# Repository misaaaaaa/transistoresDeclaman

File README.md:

# transistoresDeclaman
circuito para instalación sonora basada en compuertas NAND y sistemas imán-bobina caseros

# ruidoRupestre

**Tarjeta de presentación**

Circuito activador de sistema iman-bobina en base a circuito de compuertas NAND y 555 en modo monostable

También utilizada en obra ["Transistores en tránsito"](https://misaa.cc/projects/transistoresentransito.html) (MAC 2025), controlando bobinas suspendidas en la pared

## Revisiones

| Carpeta | Estado |
|---|---|
| [`transistoresDeclaman-rev-a/`](transistoresDeclaman-rev-a/) | Fabricada (JLC Y44-2398046A), THT. Archivos de diseño, esquemático y fotos de esa versión. Solo registro: no editar. |
| [`transistoresDeclaman-rev-b/`](transistoresDeclaman-rev-b/) | En diseño: migración a SMD con ensamblado en JLCPCB (PCBA) y corrección de los issues de rev-a. |

## flujo de trabajo (rev-b)

seguimos el [flujo de partes-jlcpcb](https://github.com/piruetasxyz/partes-jlcpcb/blob/main/flujo.md).

- [x] issues de rev-a corregidos en el esquemático (pin 5 del 555, desacople de U3, Q1)
- [x] esquemático dibujado y ERC sin errores
- [x] partes elegidas en LCSC
- [x] las que faltaban, compradas y en el inventario (ver [partes por comprar](#partes-por-comprar-rev-b-15-placas))
- [x] campo `LCSC` lleno en cada símbolo que se ensambla; `bom.csv` actualizado
- [x] biblioteca local generada con `generar_biblioteca.py` y huellas asignadas
- [x] placa diseñada, zonas rellenas
- [x] DRC sin errores, con paridad entre esquemático y placa
- [x] archivos generados con `generar_fabricacion.py` y commiteados
- [ ] vista previa de JLCPCB revisada pieza por pieza

## partes por comprar (rev-b, 15 placas)

partes que no están en el [inventario de JLCPCB](https://github.com/misaaaaaa/partes-jlcpcb-fork/blob/main/partes_updated.csv). se sacan de acá a medida que se confirma la compra. los mínimos son por placa × 15, sin repuesto: conviene sumar ~10 % y revisar el mínimo de compra de JLCPCB.

### SMD, ensambladas por JLCPCB

todas compradas y en el inventario (2026-11-27): C17673, C8678, C8512, C6986, C99124 y C2128.

### THT, soldadas a mano

| Parte | Referencias | Por placa | Mínimo (15) |
|---|---|---|---|
| CD4093BE (DIP-14), con zócalo | U1, U2 | 2 | 30 |
| LED amarillo 3 mm | D1–D7, D9, D11 | 9 | 135 |
| Trimpot 100k vertical (tipo Runtron RM-065) | RV1–RV4 | 4 | 60 |
| Jack DC horizontal | J2, J3 | 2 | 30 |
| Header 2×3, 2,54 mm | J1 | 1 | 15 |
| Header 1×2, 2,54 mm | J4 | 1 | 15 |
| Jumper 2,54 mm | J1, J4 | 2 | 30 |

## Esquemático rev-a

- Control de frecuencia de 3 osciladores por medio de trimpots

- Visualización de estados por medio de LEDS

- Poesía basada en Jussi Parikka

### Issues rev-a (JLC Y44-2398046A) 

- Pin 5 de 555 NO debe ir a tierra directamente

- Q1 tiene comportamiento extraño. No ubicar y puentear pines 2 y 3

- D13 es demasiado brillante, se recomienda no instalar. Se podría instalar una resistencia más grande en R14

- Las bobinas deben ser de alrededor de 8 a 12 ohm

## BOM rev-a

| Reference                                     | Value       | Footprint                 | Qty |
|------------------------------------------     |-------------|---------------------------|-----|
| R1,R2,R3,R5,R6,R7,R8,R10,R12,R13,~R14~,R16    | 1k          | Resistencia SMD 0805      |  12 |
| U4                                            | L7805       | Regulador TO-252          |   1 |
| U3                                       | Socket      | DIP-8                     |   1 |
| U1,U2                                    | Socket      | DIP-14                    |   2 |
| R11,R15                                  | 100k        | Resistencia THT           |   2 |
| R4,~R9~,R17                                | 10k         | Resistencia THT           |   3 |
| D4,D5,D6                                 | 1N4148      | Diodo                     |   3 |
| D11,D14                                  | 1N4007      | Diodo                     |   2 |
| Q1*,Q3                                    | 2n2222      | Transistor to-92          |   2 |
| C6,C8,C9,C11                             | 100n        | Condensador               |   4 |
| C1,C2,C3,C10                             | 100uF       | Condensador Electrolítico |   4 |
| C4,C5,C7,C12                             | 10uF        | Condensador Electrolítico |   4 |
| D1,D2,D3,D7,D8,D9,D10,D12,~D13~          | LED         | Led 3mm                   |   9 |
| J3,J5                                    | JUMPER      | Pin header 2              |   2 |
| RV1,RV2,RV3                              | 100k        | Trim RM-065               |   3 |
| Q2                                       | IRFZ44n     | Transistor to-220         |   1 |
| J1,J2                                    | Barrel_Jack | Jack DC 2.1mm             |   2 |
| J3,~J5~                                    | JUMPER      | Jumper 2p                 |   2 |
| U3                                       | NE555P      | DIP-8                     |   1 |
| U1,U2                                    | CD4093      | DIP-14                    |   2 |

\* Reemplazar por puente entre pines 2 y 3

## Expo MAC

Foto: Clo Rojo

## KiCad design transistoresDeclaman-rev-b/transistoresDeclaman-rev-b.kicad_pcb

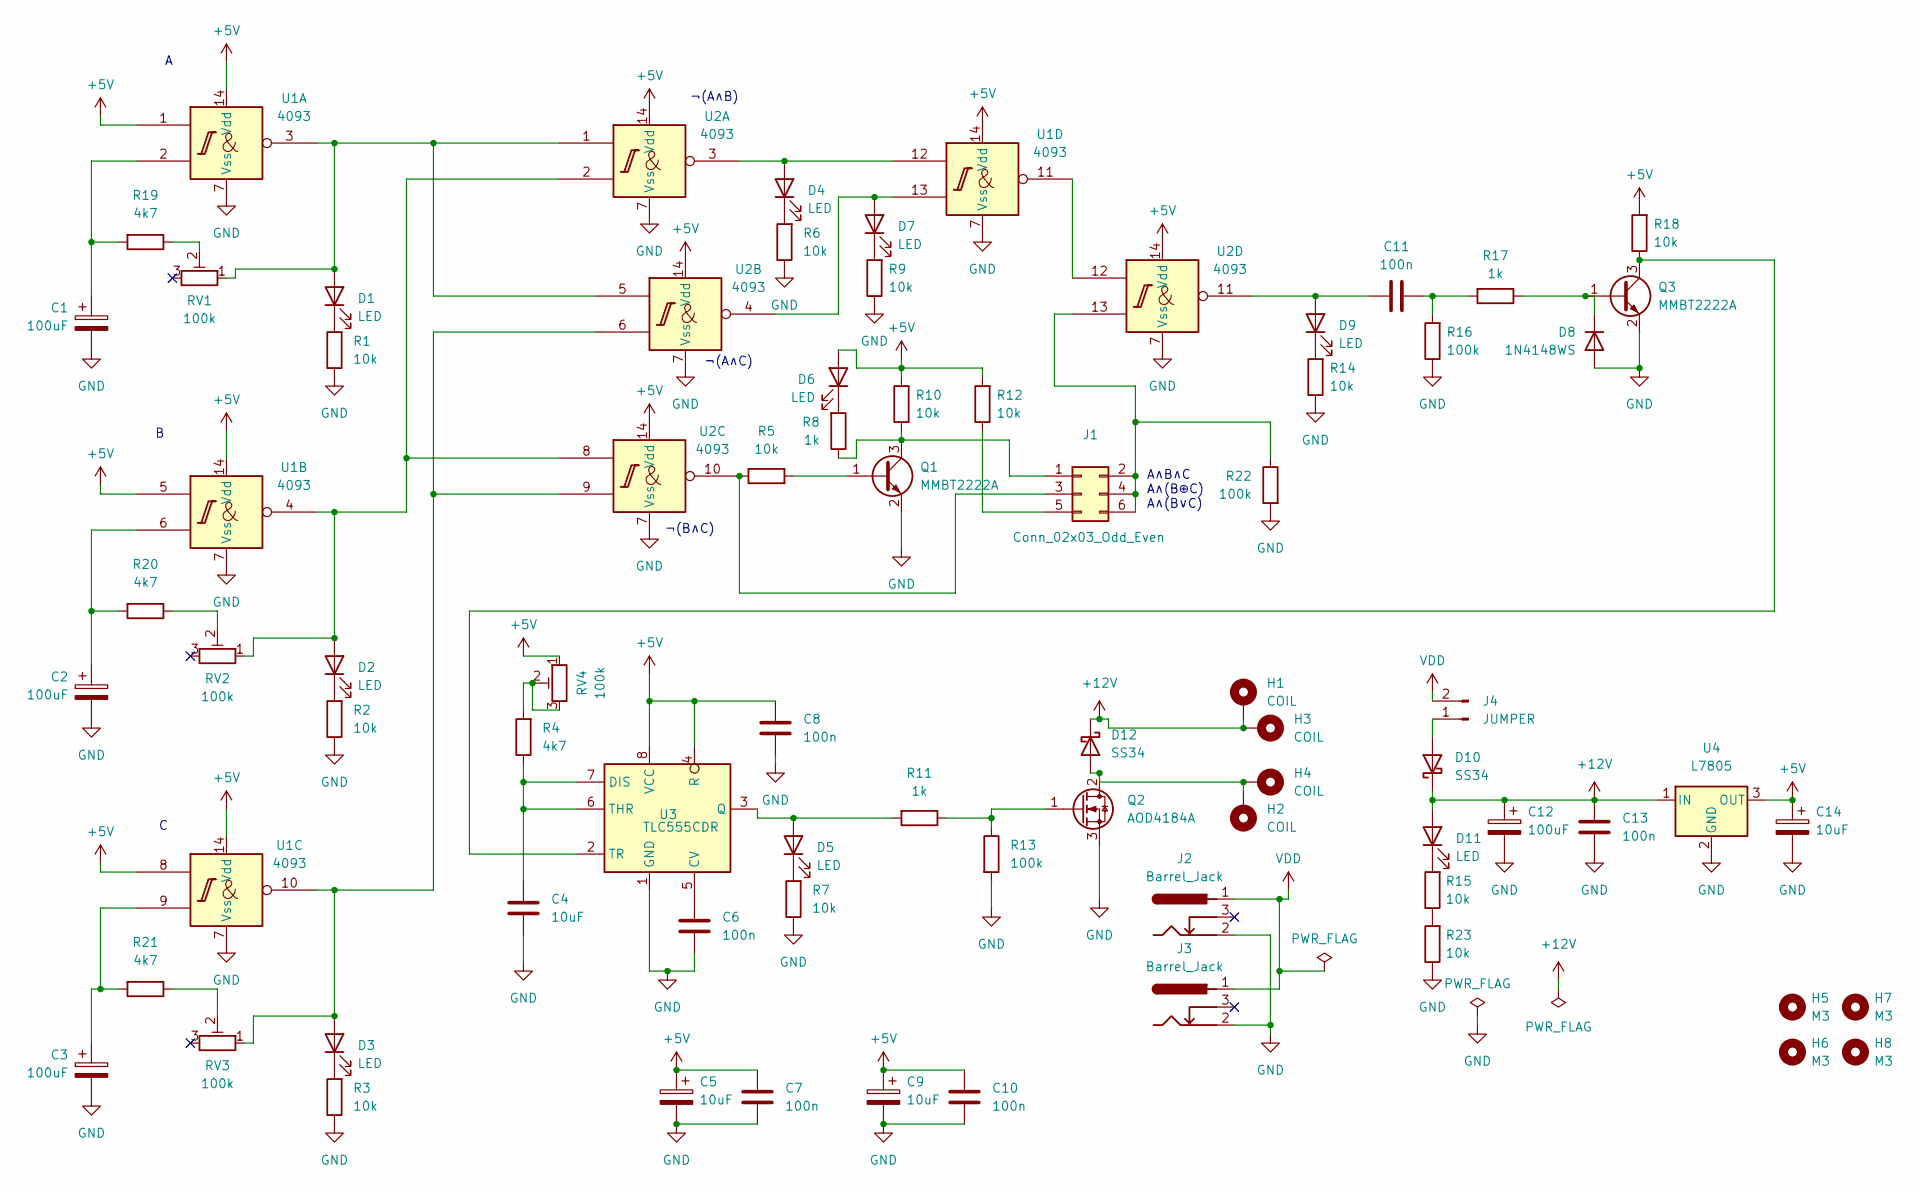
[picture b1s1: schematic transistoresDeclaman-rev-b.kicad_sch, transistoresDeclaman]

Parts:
C1, C2, C3, C12: 100uF; CAP-SMD_BD6.3-L6.6-W6.6-LS7.6-FD; LCSC C72478
C4, C5, C9, C14: 10uF; C1206; LCSC C13585
C6, C7, C8, C10, C11, C13: 100n; C0805; LCSC C49678
D1, D2, D3, D4, D5, D6, D7, D9, D11: LED; LED_PCBasDiffuser
D8: 1N4148WS; SOD-323_L1.8-W1.3-LS2.5-RD; LCSC C2128
D10, D12: SS34; SMA_L4.3-W2.6-LS5.2-RD; LCSC C8678
H1, H2: COIL; TestPoint_Pad_4.0x4.0mm
H3, H4: COIL; TestPoint_THTPad_D4.0mm_Drill2.0mm
H5, H6, H7, H8: M3; MountingHole_3.2mm_M3
J1: Conn_02x03_Odd_Even; PinHeader_2x03_P2.54mm_Vertical
J2, J3: Barrel_Jack; BarrelJack_Horizontal
J4: JUMPER; PinHeader_1x02_P2.54mm_Vertical
Q1, Q3: MMBT2222A; SOT-23-3_L2.9-W1.3-P1.90-LS2.4-BR; LCSC C8512
Q2: AOD4184A; TO-252-2_L6.6-W6.1-P4.57-LS9.9-TL-CW; LCSC C99124
R1, R2, R3, R5, R6, R7, R9, R10, R12, R14, R15, R18, R23: 10k; R0805; LCSC C17414
R4, R19, R20, R21: 4k7; R0805; LCSC C17673
R8, R11, R17: 1k; R0805; LCSC C2907232
R13, R16, R22: 100k; R0805; LCSC C25611
RV1, RV2, RV3, RV4: 100k; Potentiometer_Runtron_RM-065_Vertical
U1, U2: 4093; DIP-14_W7.62mm_LongPads
U3: TLC555CDR; SOIC-8_L5.0-W4.0-P1.27-LS6.0-BL; LCSC C6986
U4: L7805; TO-252-2_L6.6-W6.1-P4.57-LS9.9-BR-CW; LCSC C19626525

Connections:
+5V: C5.1, C7.1, C8.1, C9.1, C10.1, C14.1, D6.2 (A), R10.2, R12.2, R18.2, RV4.1, U1.1, U1.5, U1.8, U1.14 (Vdd), U2.14 (Vdd), U3.4 (R), U3.8 (VCC), U4.3 (OUT)
+12V: C12.1, C13.1, D10.1 (K), D11.2 (A), D12.1 (K), H1.1 (1_1), H3.1 (1_1), U4.1 (IN)
GND: C1.2, C2.2, C3.2, C4.2, C5.2, C6.2, C7.2, C8.2, C9.2, C10.2, C12.2, C13.2, C14.2, D8.2 (A), J2.2, J3.2, Q1.2 (E), Q2.3 (S), Q3.2 (E), R1.1, R2.1, R3.1, R6.1, R7.1, R9.1, R13.2, R14.1, R16.1, R22.2, R23.1, U1.7 (Vss), U2.7 (Vss), U3.1 (GND), U4.2 (GND)
unnamed: C1.1, R19.2, U1.2
unnamed: C2.1, R20.2, U1.6
unnamed: C3.1, R21.2, U1.9
unnamed: C11.2, R16.2, R17.2
unnamed: D1.2 (A), RV1.1, U1.3, U2.1, U2.5
unnamed: D1.1 (K), R1.2
unnamed: D2.2 (A), RV2.1, U1.4, U2.2, U2.8
unnamed: D2.1 (K), R2.2
unnamed: D3.2 (A), RV3.1, U1.10, U2.6, U2.9
unnamed: D3.1 (K), R3.2
unnamed: D4.2 (A), U1.12, U2.3
unnamed: D4.1 (K), R6.2
unnamed: D5.2 (A), R11.2, U3.3 (Q)
unnamed: D5.1 (K), R7.2
unnamed: D6.1 (K), R8.2
unnamed: D7.2 (A), U1.13, U2.4
unnamed: D7.1 (K), R9.2
unnamed: D8.1 (K), Q3.1 (B), R17.1
unnamed: C11.1, D9.2 (A), U2.11
unnamed: D9.1 (K), R14.2
unnamed: D10.2 (A), J4.1
unnamed: D11.1 (K), R15.2
unnamed: D12.2 (A), H2.1 (1_1), H4.1 (1_1), Q2.2 (D)
unnamed: J1.1, Q1.3 (C), R8.1, R10.1
unnamed: J1.2, J1.4, J1.6, R22.1, U2.13
unnamed: J1.3, R5.1, U2.10
unnamed: J1.5, R12.1
unnamed: Q1.1 (B), R5.2
unnamed: Q2.1 (G), R11.1, R13.1
unnamed: Q3.3 (C), R18.1, U3.2 (TR)
unnamed: R4.2, RV4.2, RV4.3
unnamed: R15.1, R23.2
unnamed: R19.1, RV1.2
unnamed: R20.1, RV2.2
unnamed: R21.1, RV3.2
unnamed: U1.11, U2.12
unnamed: C6.1, U3.5 (CV)
unnamed: C4.1, R4.1, U3.6 (THR), U3.7 (DIS)
VDD: J2.1, J3.1, J4.2

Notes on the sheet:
¬(A∧B)
¬(A∧C)
¬(B∧C)
A∧B∧C A∧(B⊕C) A∧(B∨C)

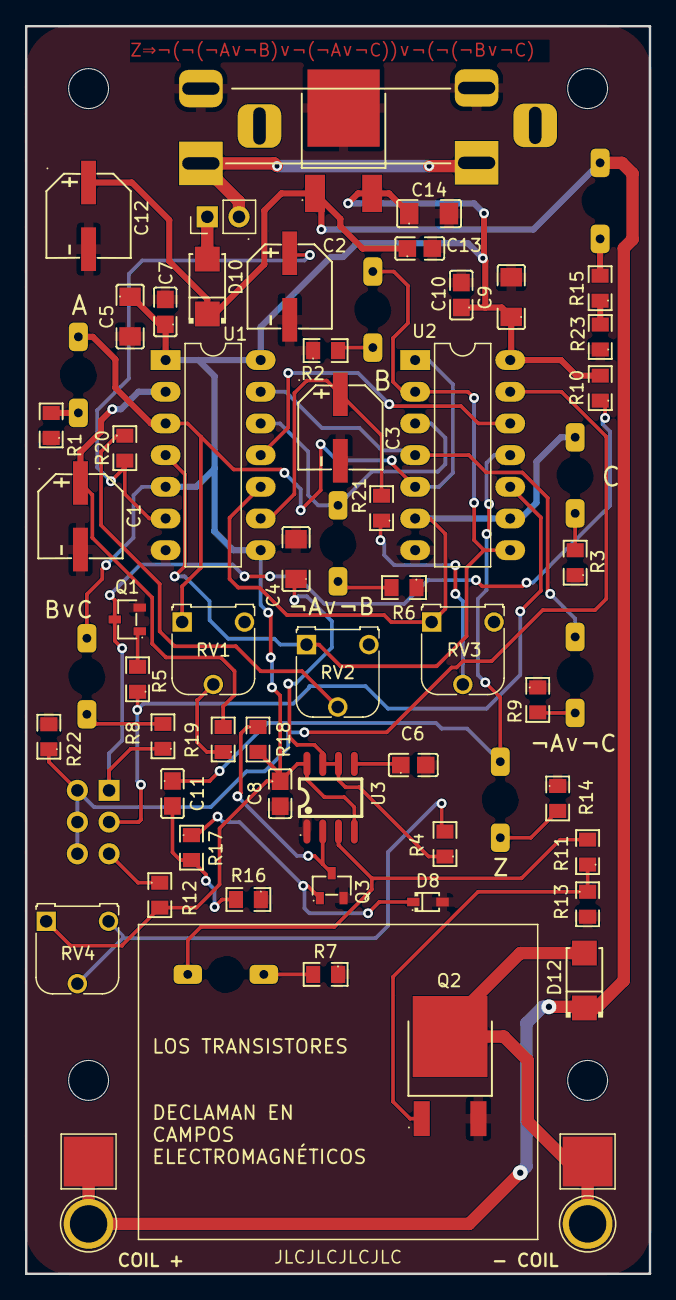
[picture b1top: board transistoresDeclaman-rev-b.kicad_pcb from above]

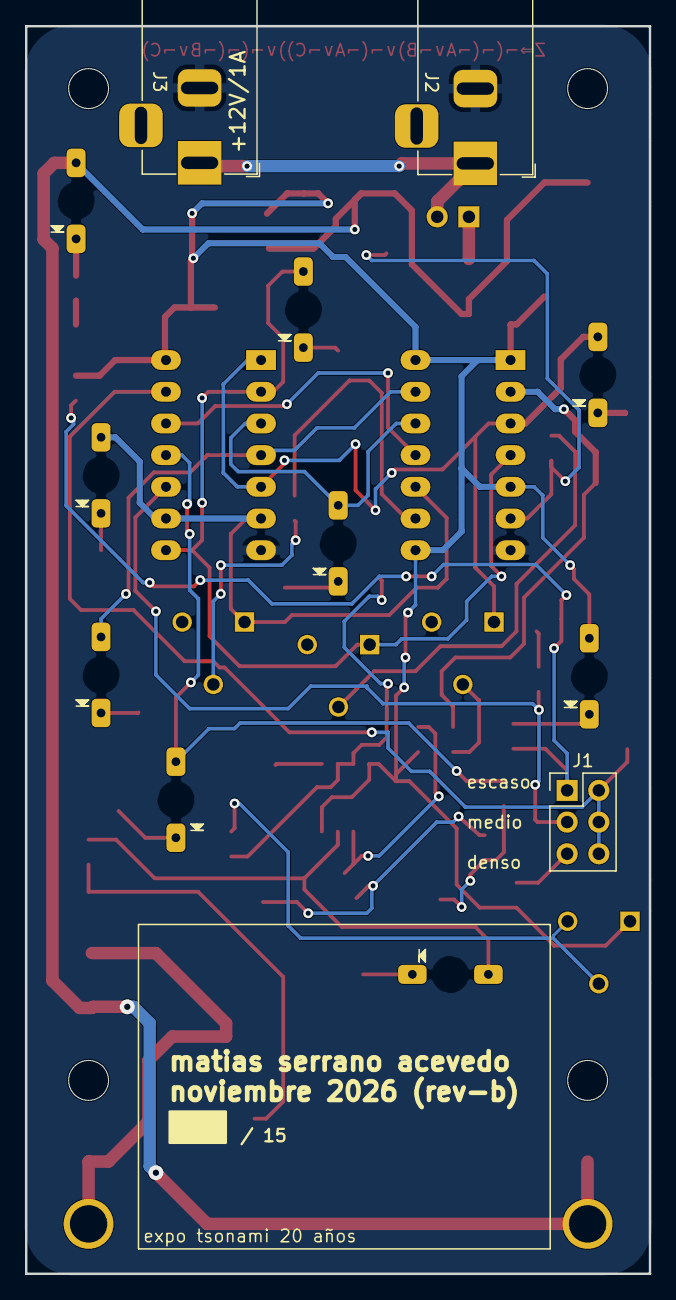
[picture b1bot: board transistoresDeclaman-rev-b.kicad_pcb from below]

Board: 2 copper layers, 50.0 x 100.0 mm, 72 parts (3 on the bottom side), 42 nets.

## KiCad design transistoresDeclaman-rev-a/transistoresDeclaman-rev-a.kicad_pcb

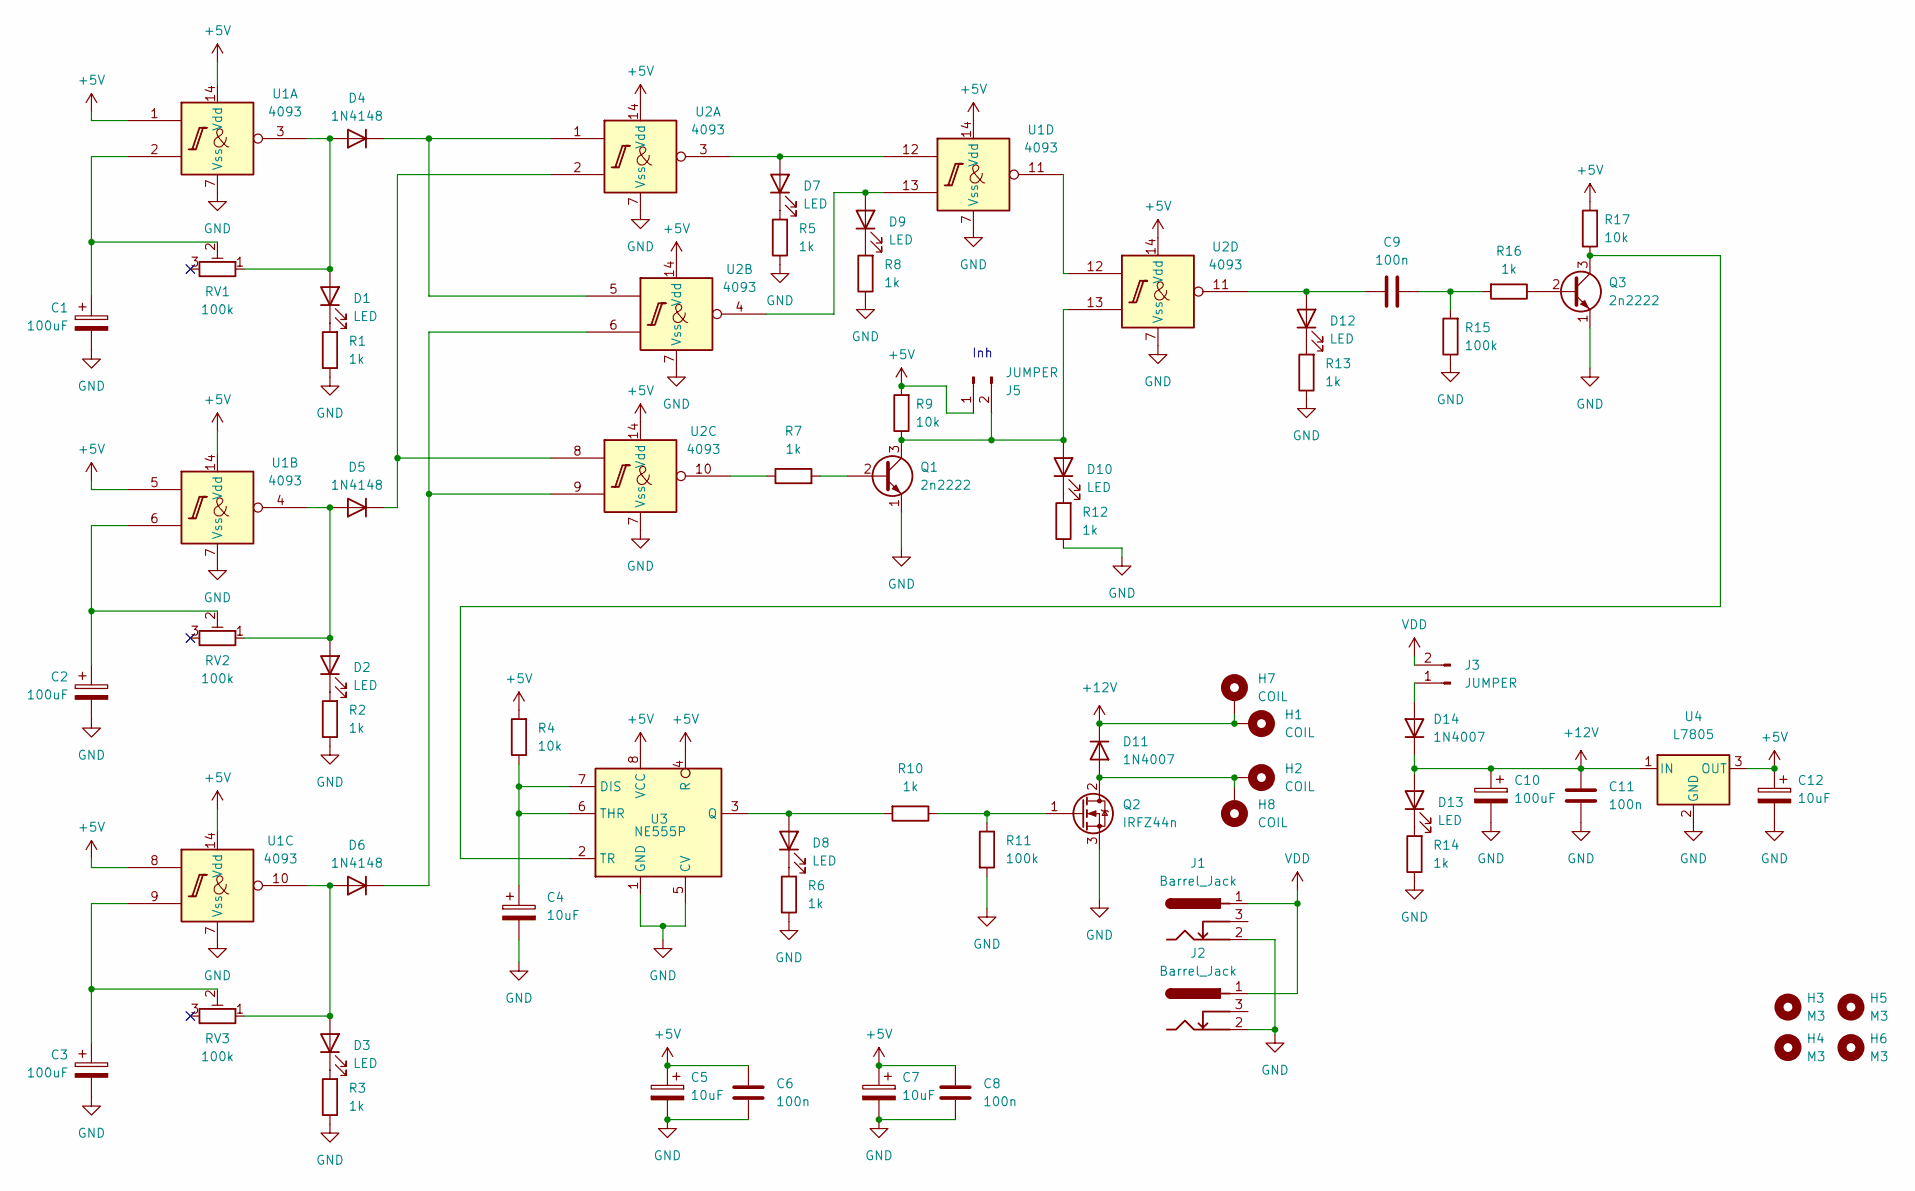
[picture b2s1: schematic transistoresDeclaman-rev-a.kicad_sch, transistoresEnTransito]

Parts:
C1, C2, C3, C10: 100uF; CP_Radial_D6.3mm_P2.50mm
C4: 10uF; CP_Radial_D6.3mm_P2.50mm
C5, C7, C12: 10uF; CP_Radial_D5.0mm_P2.50mm
C6, C8, C9, C11: 100n; C_Disc_D5.1mm_W3.2mm_P5.00mm
D1, D2, D3, D7, D8, D9, D10, D12, D13: LED; LED_PCBasDiffuser
D4, D5, D6: 1N4148; D_DO-35_SOD27_P7.62mm_Horizontal
D11, D14: 1N4007; D_DO-41_SOD81_P10.16mm_Horizontal
H1, H2: COIL; TestPoint_THTPad_D4.0mm_Drill2.0mm
H3, H4, H5, H6: M3; MountingHole_3.2mm_M3
H7, H8: COIL; TestPoint_Pad_4.0x4.0mm
J1, J2: Barrel_Jack; BarrelJack_Horizontal
J3, J5: JUMPER; PinHeader_1x02_P2.54mm_Vertical
Q1, Q3: 2n2222; TO-92_Inline_Wide
Q2: IRFZ44n; TO-220-3_Horizontal_TabDown
R1, R2, R3, R5, R6, R7, R8, R10, R12, R13, R14, R16: 1k; R_0805_2012Metric_Pad1.20x1.40mm_HandSolder
R4, R9, R17: 10k; R_Axial_DIN0207_L6.3mm_D2.5mm_P7.62mm_Horizontal
R11, R15: 100k; R_Axial_DIN0207_L6.3mm_D2.5mm_P7.62mm_Horizontal
RV1, RV2, RV3: 100k; Potentiometer_Runtron_RM-065_Vertical
U1, U2: 4093; DIP-14_W7.62mm_LongPads
U3: NE555P; DIP-8_W7.62mm
U4: L7805; TO-252-2

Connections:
+5V: C5.1, C6.1, C7.1, C8.1, C12.1, J5.1, R4.2, R9.2, R17.2, U1.1, U1.5, U1.8, U1.14 (Vdd), U2.14 (Vdd), U3.4 (R), U3.8 (VCC), U4.3 (OUT)
+12V: C10.1, C11.1, D11.1 (K), D13.2 (A), D14.1 (K), H1.1, H7.1, U4.1 (IN)
GND: C1.2, C2.2, C3.2, C4.2, C5.2, C6.2, C7.2, C8.2, C10.2, C11.2, C12.2, J1.2, J2.2, Q1.1 (E), Q2.3 (S), Q3.1 (E), R1.1, R2.1, R3.1, R5.1, R6.1, R8.1, R11.2, R12.1, R13.1, R14.1, R15.1, U1.7 (Vss), U2.7 (Vss), U3.1 (GND), U3.5 (CV), U4.2 (GND)
unnamed: C1.1, RV1.2, U1.2
unnamed: C2.1, RV2.2, U1.6
unnamed: C3.1, RV3.2, U1.9
unnamed: C9.2, R15.2, R16.2
unnamed: D1.2 (A), D4.2 (A), RV1.1, U1.3
unnamed: D1.1 (K), R1.2
unnamed: D2.2 (A), D5.2 (A), RV2.1, U1.4
unnamed: D2.1 (K), R2.2
unnamed: D3.2 (A), D6.2 (A), RV3.1, U1.10
unnamed: D3.1 (K), R3.2
unnamed: D4.1 (K), U2.1, U2.5
unnamed: D5.1 (K), U2.2, U2.8
unnamed: D6.1 (K), U2.6, U2.9
unnamed: D7.2 (A), U1.12, U2.3
unnamed: D7.1 (K), R5.2
unnamed: D8.2 (A), R10.2, U3.3 (Q)
unnamed: D8.1 (K), R6.2
unnamed: D9.2 (A), U1.13, U2.4
unnamed: D9.1 (K), R8.2
unnamed: D10.2 (A), J5.2, Q1.3 (C), R9.1, U2.13
unnamed: D10.1 (K), R12.2
unnamed: D11.2 (A), H2.1, H8.1, Q2.2 (D)
unnamed: C9.1, D12.2 (A), U2.11
unnamed: D12.1 (K), R13.2
unnamed: D13.1 (K), R14.2
unnamed: D14.2 (A), J3.1
unnamed: Q1.2 (B), R7.2
unnamed: Q2.1 (G), R10.1, R11.1
unnamed: Q3.2 (B), R16.1
unnamed: Q3.3 (C), R17.1, U3.2 (TR)
unnamed: R7.1, U2.10
unnamed: U1.11, U2.12
unnamed: C4.1, R4.1, U3.6 (THR), U3.7 (DIS)
VDD: J1.1, J2.1, J3.2

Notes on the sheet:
Inh

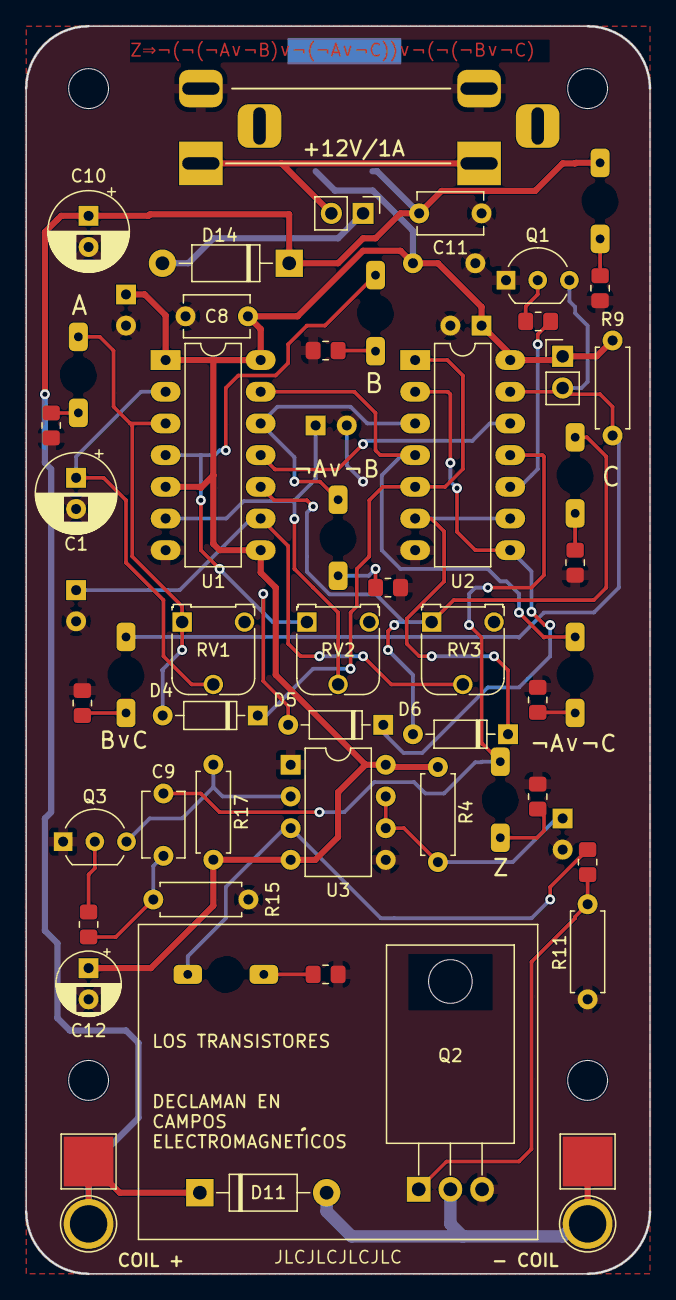
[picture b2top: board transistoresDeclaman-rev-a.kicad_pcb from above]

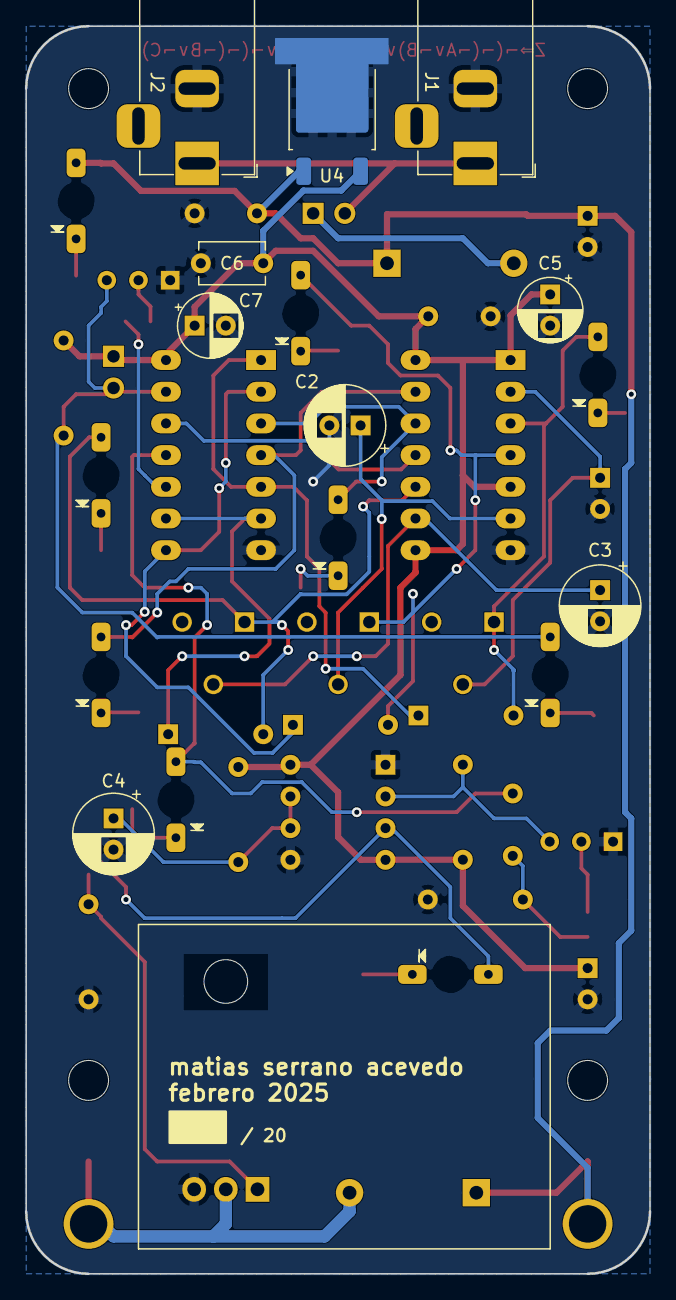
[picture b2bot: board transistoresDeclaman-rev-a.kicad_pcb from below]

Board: 2 copper layers, 50.0 x 100.0 mm, 65 parts (9 on the bottom side), 37 nets.
